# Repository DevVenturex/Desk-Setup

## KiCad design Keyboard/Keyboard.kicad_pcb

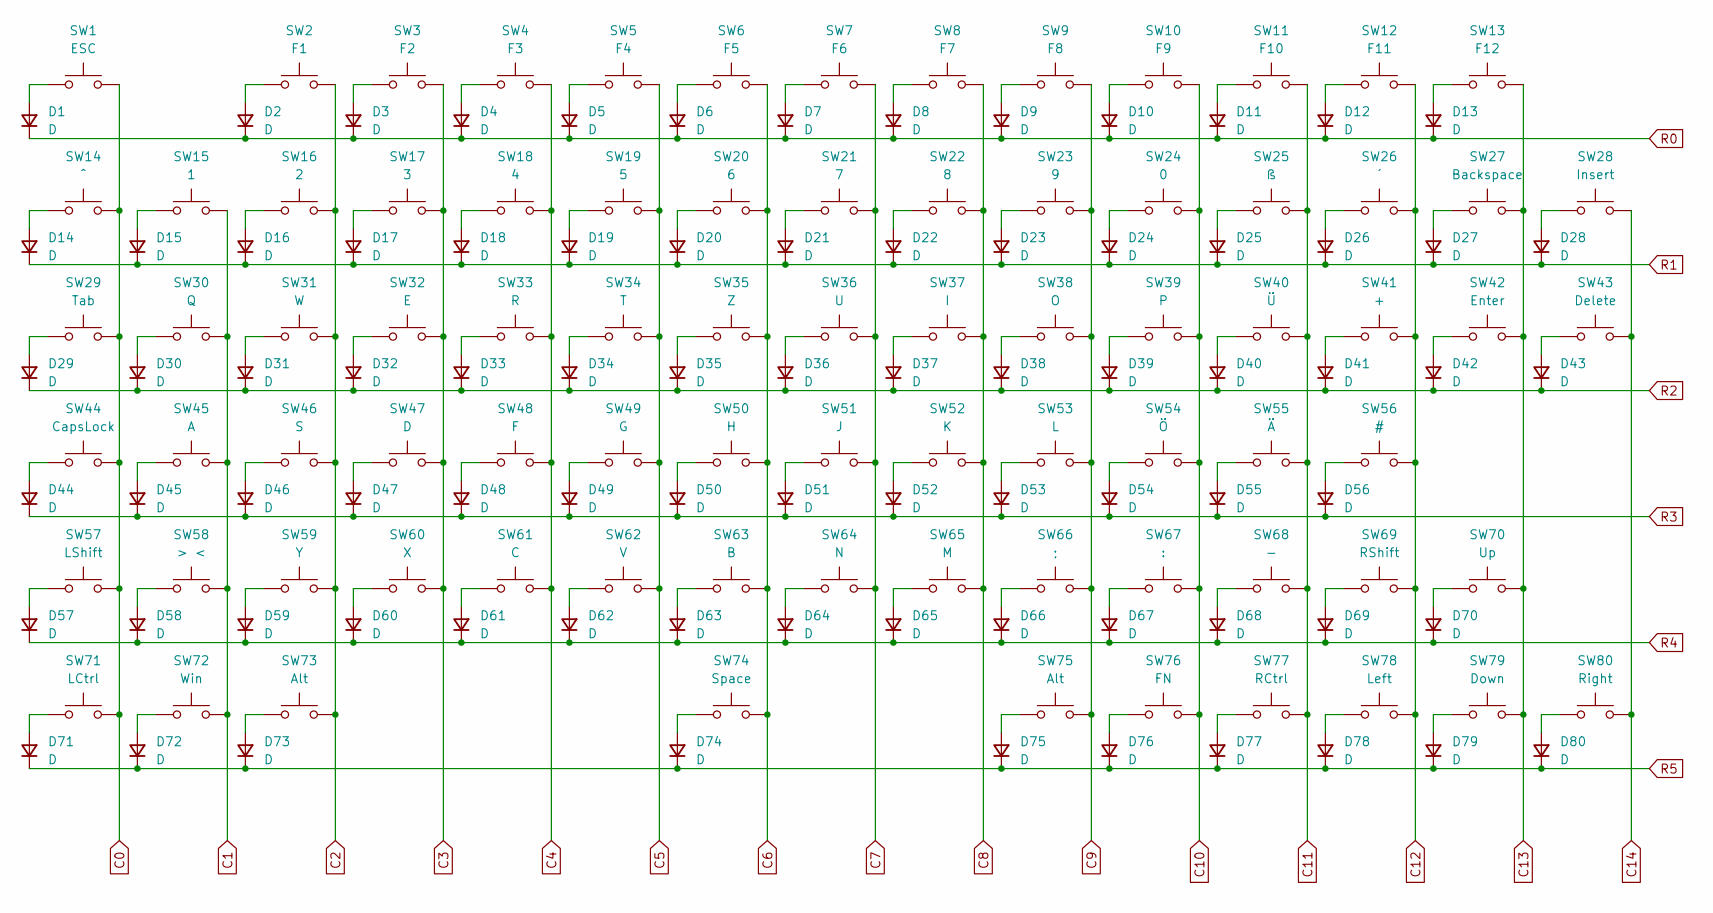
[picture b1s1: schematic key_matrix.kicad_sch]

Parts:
D1, D2, D3, D4, D5, D6, D7, D8, D9, D10, D11, D12, D13, D14, D15, D16, D17, D18, D19, D20, D21, D22, D23, D24, D25, D26, D27, D28, D29, D30, D31, D32, D33, D34, D35, D36, D37, D38, D39, D40, D41, D42, D43, D44, D45, D46, D47, D48, D49, D50, D51, D52, D53, D54, D55, D56, D57, D58, D59, D60, D61, D62, D63, D64, D65, D66, D67, D68, D69, D70, D71, D72, D73, D74, D75, D76, D77, D78, D79, D80: D; D_SOD-123
SW1: ESC; SW_Hotswap_Kailh_MX_1.00u
SW2: F1; SW_Hotswap_Kailh_MX_1.00u
SW3: F2; SW_Hotswap_Kailh_MX_1.00u
SW4: F3; SW_Hotswap_Kailh_MX_1.00u
SW5: F4; SW_Hotswap_Kailh_MX_1.00u
SW6: F5; SW_Hotswap_Kailh_MX_1.00u
SW7: F6; SW_Hotswap_Kailh_MX_1.00u
SW8: F7; SW_Hotswap_Kailh_MX_1.00u
SW9: F8; SW_Hotswap_Kailh_MX_1.00u
SW10: F9; SW_Hotswap_Kailh_MX_1.00u
SW11: F10; SW_Hotswap_Kailh_MX_1.00u
SW12: F11; SW_Hotswap_Kailh_MX_1.00u
SW13: F12; SW_Hotswap_Kailh_MX_1.00u
SW14: ^; SW_Hotswap_Kailh_MX_1.00u
SW15: 1; SW_Hotswap_Kailh_MX_1.00u
SW16: 2; SW_Hotswap_Kailh_MX_1.00u
SW17: 3; SW_Hotswap_Kailh_MX_1.00u
SW18: 4; SW_Hotswap_Kailh_MX_1.00u
SW19: 5; SW_Hotswap_Kailh_MX_1.00u
SW20: 6; SW_Hotswap_Kailh_MX_1.00u
SW21: 7; SW_Hotswap_Kailh_MX_1.00u
SW22: 8; SW_Hotswap_Kailh_MX_1.00u
SW23: 9; SW_Hotswap_Kailh_MX_1.00u
SW24: 0; SW_Hotswap_Kailh_MX_1.00u
SW25: ß; SW_Hotswap_Kailh_MX_1.00u
SW26: ´; SW_Hotswap_Kailh_MX_1.00u
SW27: Backspace; SW_Hotswap_Kailh_MX_2.00u
SW28: Insert; SW_Hotswap_Kailh_MX_1.00u
SW29: Tab; SW_Hotswap_Kailh_MX_1.50u
SW30: Q; SW_Hotswap_Kailh_MX_1.00u
SW31: W; SW_Hotswap_Kailh_MX_1.00u
SW32: E; SW_Hotswap_Kailh_MX_1.00u
SW33: R; SW_Hotswap_Kailh_MX_1.00u
SW34: T; SW_Hotswap_Kailh_MX_1.00u
SW35: Z; SW_Hotswap_Kailh_MX_1.00u
SW36: U; SW_Hotswap_Kailh_MX_1.00u
SW37: I; SW_Hotswap_Kailh_MX_1.00u
SW38: O; SW_Hotswap_Kailh_MX_1.00u
SW39: P; SW_Hotswap_Kailh_MX_1.00u
SW40: Ü; SW_Hotswap_Kailh_MX_1.00u
SW41: +; SW_Hotswap_Kailh_MX_1.00u
SW42: Enter; SW_Hotswap_Kailh_MX_ISOEnter
SW43: Delete; SW_Hotswap_Kailh_MX_1.00u
SW44: CapsLock; SW_Hotswap_Kailh_MX_1.75u
SW45: A; SW_Hotswap_Kailh_MX_1.00u
SW46: S; SW_Hotswap_Kailh_MX_1.00u
SW47: D; SW_Hotswap_Kailh_MX_1.00u
SW48: F; SW_Hotswap_Kailh_MX_1.00u
SW49: G; SW_Hotswap_Kailh_MX_1.00u
SW50: H; SW_Hotswap_Kailh_MX_1.00u
SW51: J; SW_Hotswap_Kailh_MX_1.00u
SW52: K; SW_Hotswap_Kailh_MX_1.00u
SW53: L; SW_Hotswap_Kailh_MX_1.00u
SW54: Ö; SW_Hotswap_Kailh_MX_1.00u
SW55: Ä; SW_Hotswap_Kailh_MX_1.00u
SW56: #; SW_Hotswap_Kailh_MX_1.00u
SW57: LShift; SW_Hotswap_Kailh_MX_1.25u
SW58: > <; SW_Hotswap_Kailh_MX_1.00u
SW59: Y; SW_Hotswap_Kailh_MX_1.00u
SW60: X; SW_Hotswap_Kailh_MX_1.00u
SW61: C; SW_Hotswap_Kailh_MX_1.00u
SW62: V; SW_Hotswap_Kailh_MX_1.00u
SW63: B; SW_Hotswap_Kailh_MX_1.00u
SW64: N; SW_Hotswap_Kailh_MX_1.00u
SW65: M; SW_Hotswap_Kailh_MX_1.00u
SW66: ;; SW_Hotswap_Kailh_MX_1.00u
SW67: :; SW_Hotswap_Kailh_MX_1.00u
SW68: -; SW_Hotswap_Kailh_MX_1.00u
SW69: RShift; SW_Hotswap_Kailh_MX_2.25u
SW70: Up; SW_Hotswap_Kailh_MX_1.00u
SW71: LCtrl; SW_Hotswap_Kailh_MX_1.25u
SW72: Win; SW_Hotswap_Kailh_MX_1.00u
SW73, SW75: Alt; SW_Hotswap_Kailh_MX_1.25u
SW74: Space; SW_Hotswap_Kailh_MX_6.25u
SW76: FN; SW_Hotswap_Kailh_MX_1.25u
SW77: RCtrl; SW_Hotswap_Kailh_MX_1.25u
SW78: Left; SW_Hotswap_Kailh_MX_1.00u
SW79: Down; SW_Hotswap_Kailh_MX_1.00u
SW80: Right; SW_Hotswap_Kailh_MX_1.00u

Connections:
C0: SW1.2, SW14.2, SW29.2, SW44.2, SW57.2, SW71.2
C1: SW15.2, SW30.2, SW45.2, SW58.2, SW72.2
C2: SW2.2, SW16.2, SW31.2, SW46.2, SW59.2, SW73.2
C3: SW3.2, SW17.2, SW32.2, SW47.2, SW60.2
C4: SW4.2, SW18.2, SW33.2, SW48.2, SW61.2
C5: SW5.2, SW19.2, SW34.2, SW49.2, SW62.2
C6: SW6.2, SW20.2, SW35.2, SW50.2, SW63.2, SW74.2
C7: SW7.2, SW21.2, SW36.2, SW51.2, SW64.2
C8: SW8.2, SW22.2, SW37.2, SW52.2, SW65.2
C9: SW9.2, SW23.2, SW38.2, SW53.2, SW66.2, SW75.2
C10: SW10.2, SW24.2, SW39.2, SW54.2, SW67.2, SW76.2
C11: SW11.2, SW25.2, SW40.2, SW55.2, SW68.2, SW77.2
C12: SW12.2, SW26.2, SW41.2, SW56.2, SW69.2, SW78.2
C13: SW13.2, SW27.2, SW42.2, SW70.2, SW79.2
C14: SW28.2, SW43.2, SW80.2
unnamed: D1.2 (A), SW1.1
unnamed: D2.2 (A), SW2.1
unnamed: D3.2 (A), SW3.1
unnamed: D4.2 (A), SW4.1
unnamed: D5.2 (A), SW5.1
unnamed: D6.2 (A), SW6.1
unnamed: D7.2 (A), SW7.1
unnamed: D8.2 (A), SW8.1
unnamed: D9.2 (A), SW9.1
unnamed: D10.2 (A), SW10.1
unnamed: D11.2 (A), SW11.1
unnamed: D12.2 (A), SW12.1
unnamed: D13.2 (A), SW13.1
unnamed: D14.2 (A), SW14.1
unnamed: D15.2 (A), SW15.1
unnamed: D16.2 (A), SW16.1
unnamed: D17.2 (A), SW17.1
unnamed: D18.2 (A), SW18.1
unnamed: D19.2 (A), SW19.1
unnamed: D20.2 (A), SW20.1
unnamed: D21.2 (A), SW21.1
unnamed: D22.2 (A), SW22.1
unnamed: D23.2 (A), SW23.1
unnamed: D24.2 (A), SW24.1
unnamed: D25.2 (A), SW25.1
unnamed: D26.2 (A), SW26.1
unnamed: D27.2 (A), SW27.1
unnamed: D28.2 (A), SW28.1
unnamed: D29.2 (A), SW29.1
unnamed: D30.2 (A), SW30.1
unnamed: D31.2 (A), SW31.1
unnamed: D32.2 (A), SW32.1
unnamed: D33.2 (A), SW33.1
unnamed: D34.2 (A), SW34.1
unnamed: D35.2 (A), SW35.1
unnamed: D36.2 (A), SW36.1
unnamed: D37.2 (A), SW37.1
unnamed: D38.2 (A), SW38.1
unnamed: D39.2 (A), SW39.1
unnamed: D40.2 (A), SW40.1
unnamed: D41.2 (A), SW41.1
unnamed: D42.2 (A), SW42.1
unnamed: D43.2 (A), SW43.1
unnamed: D44.2 (A), SW44.1
unnamed: D45.2 (A), SW45.1
unnamed: D46.2 (A), SW46.1
unnamed: D47.2 (A), SW47.1
unnamed: D48.2 (A), SW48.1
unnamed: D49.2 (A), SW49.1
unnamed: D50.2 (A), SW50.1
unnamed: D51.2 (A), SW51.1
unnamed: D52.2 (A), SW52.1
unnamed: D53.2 (A), SW53.1
unnamed: D54.2 (A), SW54.1
unnamed: D55.2 (A), SW55.1
unnamed: D56.2 (A), SW56.1
unnamed: D57.2 (A), SW57.1
unnamed: D58.2 (A), SW58.1
unnamed: D59.2 (A), SW59.1
unnamed: D60.2 (A), SW60.1
unnamed: D61.2 (A), SW61.1
unnamed: D62.2 (A), SW62.1
unnamed: D63.2 (A), SW63.1
unnamed: D64.2 (A), SW64.1
unnamed: D65.2 (A), SW65.1
unnamed: D66.2 (A), SW66.1
unnamed: D67.2 (A), SW67.1
unnamed: D68.2 (A), SW68.1
unnamed: D69.2 (A), SW69.1
unnamed: D70.2 (A), SW70.1
unnamed: D71.2 (A), SW71.1
unnamed: D72.2 (A), SW72.1
unnamed: D73.2 (A), SW73.1
unnamed: D74.2 (A), SW74.1
unnamed: D75.2 (A), SW75.1
unnamed: D76.2 (A), SW76.1
unnamed: D77.2 (A), SW77.1
unnamed: D78.2 (A), SW78.1
unnamed: D79.2 (A), SW79.1
unnamed: D80.2 (A), SW80.1
R0: D1.1 (K), D2.1 (K), D3.1 (K), D4.1 (K), D5.1 (K), D6.1 (K), D7.1 (K), D8.1 (K), D9.1 (K), D10.1 (K), D11.1 (K), D12.1 (K), D13.1 (K)
R1: D14.1 (K), D15.1 (K), D16.1 (K), D17.1 (K), D18.1 (K), D19.1 (K), D20.1 (K), D21.1 (K), D22.1 (K), D23.1 (K), D24.1 (K), D25.1 (K), D26.1 (K), D27.1 (K), D28.1 (K)
R2: D29.1 (K), D30.1 (K), D31.1 (K), D32.1 (K), D33.1 (K), D34.1 (K), D35.1 (K), D36.1 (K), D37.1 (K), D38.1 (K), D39.1 (K), D40.1 (K), D41.1 (K), D42.1 (K), D43.1 (K)
R3: D44.1 (K), D45.1 (K), D46.1 (K), D47.1 (K), D48.1 (K), D49.1 (K), D50.1 (K), D51.1 (K), D52.1 (K), D53.1 (K), D54.1 (K), D55.1 (K), D56.1 (K)
R4: D57.1 (K), D58.1 (K), D59.1 (K), D60.1 (K), D61.1 (K), D62.1 (K), D63.1 (K), D64.1 (K), D65.1 (K), D66.1 (K), D67.1 (K), D68.1 (K), D69.1 (K), D70.1 (K)
R5: D71.1 (K), D72.1 (K), D73.1 (K), D74.1 (K), D75.1 (K), D76.1 (K), D77.1 (K), D78.1 (K), D79.1 (K), D80.1 (K)

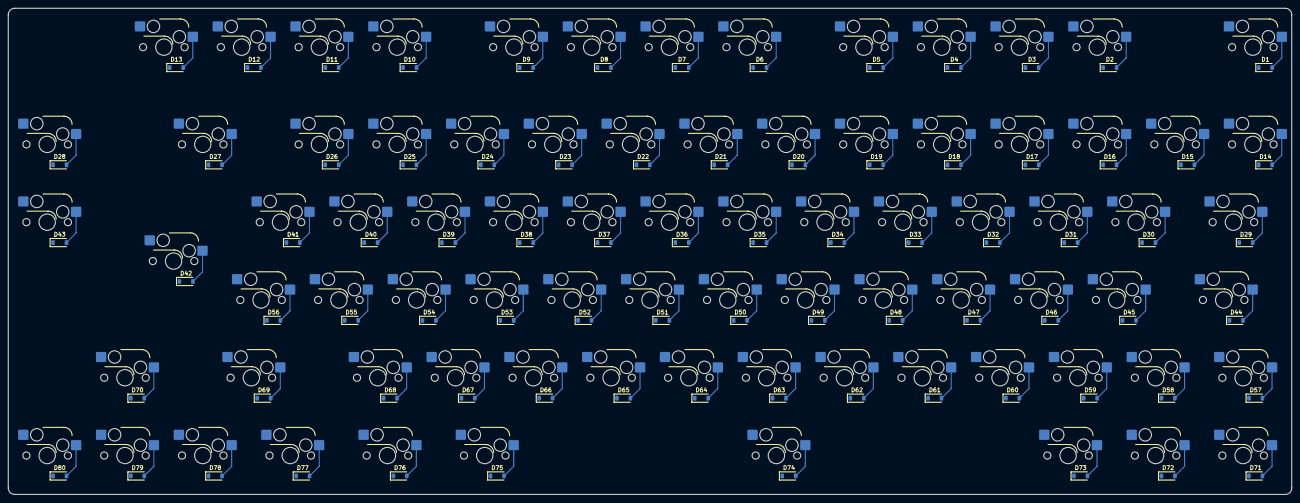
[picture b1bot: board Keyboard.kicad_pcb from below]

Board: 4 copper layers, 314.3 x 119.1 mm, 160 parts (80 on the bottom side), 101 nets.

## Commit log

2024-06-30 Key Layout
